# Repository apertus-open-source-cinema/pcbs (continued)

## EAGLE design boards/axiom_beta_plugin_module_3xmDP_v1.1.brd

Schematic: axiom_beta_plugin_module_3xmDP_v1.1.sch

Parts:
C1: C0402-B; 0402-B
C2, C3, C4, C5, C6, C7: C0603-B; 0603-B
LED1, LED2, LED3, LED4, LED5, LED6: LEDCHIPLED_0603; CHIPLED_0603
PCIE-NORTH: PCIE-36-AXIOM
PCIE-SOUTH: PCIE-36-AXIOM
R1: 10k; 0402-B
R2: 1k; 0402-B
R3, R4, R5, R6, R7, R8: R0402-B; 0402-B
U1: BR24G04NUX; DFN200X300X100-9N
U2, U3, U4: MIC209X; SOT95P280X145-5N
X1, X2, X3: MINI-DP-ADIS0013; ADIS0013

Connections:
C_!FAULT: LED4.C, U3.4 (!FAULT)
C_AUX_N: PCIE-NORTH.B9 (IO5), X2.17
C_AUX_P: PCIE-NORTH.B8 (IO4), X2.15
C_EN: PCIE-SOUTH.B11 (IO7), R5.1, U3.3 (EN)
C_HPD: PCIE-SOUTH.B10 (IO6), X2.18
C_ML0_N: PCIE-SOUTH.A17 (LVDS_4B), X2.3
C_ML0_P: PCIE-SOUTH.A16 (LVDS_4A), X2.1
C_ML1_N: PCIE-NORTH.A3 (LVDS_0B), X2.6
C_ML1_P: PCIE-NORTH.A2 (LVDS_0A), X2.4
C_ML2_N: PCIE-SOUTH.B17 (LVDS_5B), X2.9
C_ML2_P: PCIE-SOUTH.B16 (LVDS_5A), X2.7
C_ML3_N: PCIE-NORTH.A6 (LVDS_1B), X2.12
C_ML3_P: PCIE-NORTH.A5 (LVDS_1A), X2.10
C_PWR: C5.1, U3.5 (VOUT), X2.20
GND: C1.2, C2.2, C3.2, C4.2, C5.2, C6.2, C7.2, LED1.C, LED3.C, LED5.C, PCIE-NORTH.A1 (GND), PCIE-NORTH.A4 (GND), PCIE-NORTH.A7 (GND), PCIE-NORTH.A10 (GND), PCIE-NORTH.A12 (GND), PCIE-NORTH.A15 (GND), PCIE-NORTH.A18 (GND), PCIE-NORTH.B15 (GND), PCIE-NORTH.B18 (GND), PCIE-SOUTH.A1 (GND), PCIE-SOUTH.A4 (GND), PCIE-SOUTH.A7 (GND), PCIE-SOUTH.A10 (GND), PCIE-SOUTH.A12 (GND), PCIE-SOUTH.A15 (GND), PCIE-SOUTH.A18 (GND), PCIE-SOUTH.B15 (GND), PCIE-SOUTH.B18 (GND), R2.2, U1.1 (A0), U1.2 (A1), U1.3 (A2), U1.4 (GND), U1.EP, U2.2 (GND), U3.2 (GND), U4.2 (GND), X1.2, X1.5, X1.8, X1.11, X1.13, X1.14, X1.16, X1.19, X1.H1 (M), X1.H2 (M), X1.H3 (M), X1.H4 (M), X2.2, X2.5, X2.8, X2.11, X2.13, X2.14, X2.16, X2.19, X2.H1 (M), X2.H2 (M), X2.H3 (M), X2.H4 (M), X3.2, X3.5, X3.8, X3.11, X3.13, X3.14, X3.16, X3.19, X3.H1 (M), X3.H2 (M), X3.H3 (M), X3.H4 (M)
I2C_V: C1.1, PCIE-NORTH.B3 (V_I2C), R1.1, U1.8 (VCC)
unnamed: LED3.A, R5.2
unnamed: LED4.A, R6.2
unnamed: LED1.A, R3.2
unnamed: LED2.A, R4.2
unnamed: R1.2, R2.1, U1.7 (WP)
unnamed: LED5.A, R7.2
unnamed: LED6.A, R8.2
N_5V: PCIE-NORTH.B12 (5V)
N_!FAULT: LED2.C, U2.4 (!FAULT)
N_AUX_N: PCIE-NORTH.B11 (IO7), X1.17
N_AUX_P: PCIE-NORTH.B10 (IO6), X1.15
N_EN: PCIE-NORTH.B5 (IO1), R3.1, U2.3 (EN)
N_HPD: PCIE-NORTH.B4 (IO0), X1.18
N_ML0_N: PCIE-NORTH.A9 (LVDS_2B), X1.3
N_ML0_P: PCIE-NORTH.A8 (LVDS_2A), X1.1
N_ML1_N: PCIE-NORTH.A14 (LVDS_3B), X1.6
N_ML1_P: PCIE-NORTH.A13 (LVDS_3A), X1.4
N_ML2_N: PCIE-NORTH.B17 (LVDS_5B), X1.9
N_ML2_P: PCIE-NORTH.B16 (LVDS_5A), X1.7
N_ML3_N: PCIE-NORTH.A17 (LVDS_4B), X1.12
N_ML3_P: PCIE-NORTH.A16 (LVDS_4A), X1.10
N_PCIE_V: C2.1, C4.1, PCIE-NORTH.B13 (VCC), R4.1, R6.1, U2.1 (VIN), U3.1 (VIN)
N_PWR: C3.1, U2.5 (VOUT), X1.20
N_VCCIO: PCIE-NORTH.B14 (VCCIO)
SCL: PCIE-NORTH.B2 (SCL), U1.6 (SCL)
SDA: PCIE-NORTH.B1 (SDA), U1.5 (SDA)
S_5V: PCIE-SOUTH.B12 (5V)
S_!FAULT: LED6.C, U4.4 (!FAULT)
S_AUX_N: PCIE-NORTH.B7 (IO3), X3.17
S_AUX_P: PCIE-NORTH.B6 (IO2), X3.15
S_EN: PCIE-SOUTH.B5 (IO1), R7.1, U4.3 (EN)
S_HPD: PCIE-SOUTH.B4 (IO0), X3.18
S_IO2: PCIE-SOUTH.B6 (IO2)
S_IO3: PCIE-SOUTH.B7 (IO3)
S_IO4: PCIE-SOUTH.B8 (IO4)
S_IO5: PCIE-SOUTH.B9 (IO5)
S_ML0_N: PCIE-SOUTH.A3 (LVDS_0B), X3.3
S_ML0_P: PCIE-SOUTH.A2 (LVDS_0A), X3.1
S_ML1_N: PCIE-SOUTH.A6 (LVDS_1B), X3.6
S_ML1_P: PCIE-SOUTH.A5 (LVDS_1A), X3.4
S_ML2_N: PCIE-SOUTH.A14 (LVDS_3B), X3.9
S_ML2_P: PCIE-SOUTH.A13 (LVDS_3A), X3.7
S_ML3_N: PCIE-SOUTH.A9 (LVDS_2B), X3.12
S_ML3_P: PCIE-SOUTH.A8 (LVDS_2A), X3.10
S_PCIE_V: C6.1, PCIE-SOUTH.B13 (VCC), R8.1, U4.1 (VIN)
S_PWR: C7.1, U4.5 (VOUT), X3.20
S_VCCIO: PCIE-SOUTH.B14 (VCCIO)

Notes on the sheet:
AXIOM Beta Module
Copyright (C) 2015 H.Poetzl Licensed under CERN OHL v.1.2
Tripe PMOD Plugin Module
Info EEPROM
North DisplayPort
Center DisplayPort
South DisplayPort

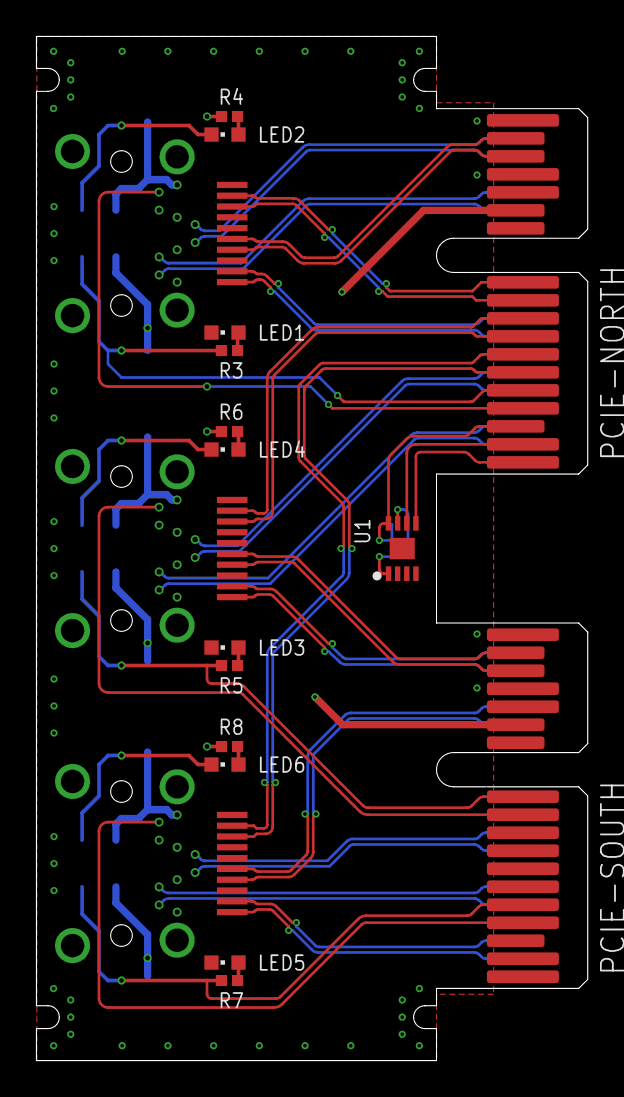
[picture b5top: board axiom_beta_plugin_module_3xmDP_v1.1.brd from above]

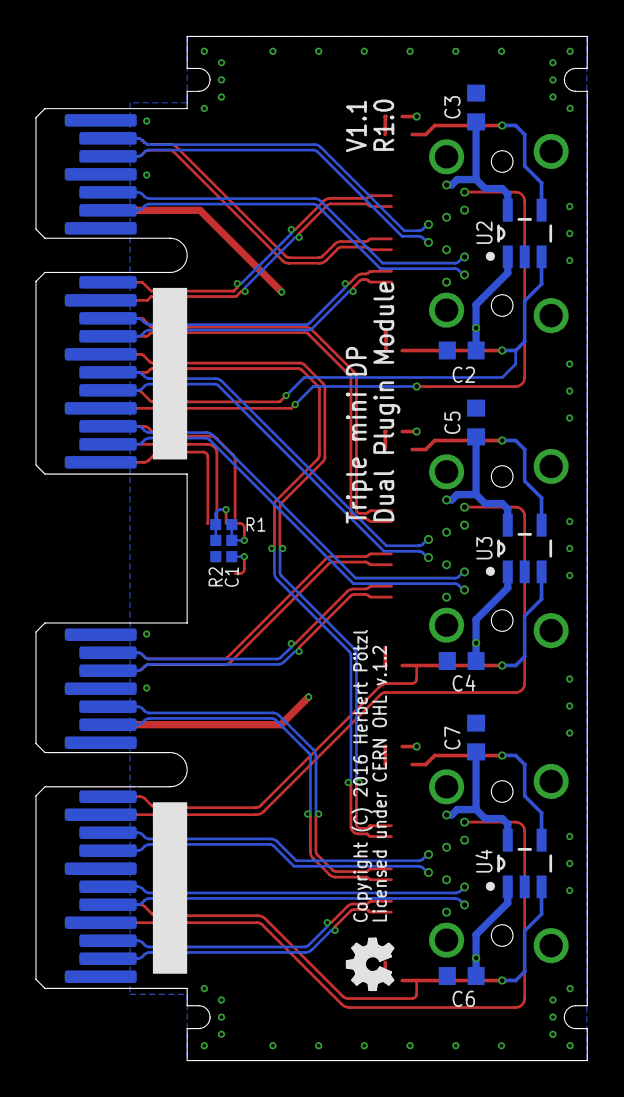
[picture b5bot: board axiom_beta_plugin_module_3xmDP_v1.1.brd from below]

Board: 4 copper layers, 30.6 x 56.9 mm, 31 parts (13 on the bottom side), 55 nets.

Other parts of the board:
LOGO1: OSHW_LOGO_FILLX0100-NT; OSHW_FILLX100_NOTEXT

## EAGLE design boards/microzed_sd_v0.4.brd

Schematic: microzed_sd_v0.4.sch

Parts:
C1, C2, C3, C4, C6: 1µ; C0402K
C5: 2n2; C0402K
D1: DIODE-MICROMELF-W; MICROMELF-W
DN: TPTP20R; TP20R
DP: TPTP20R; TP20R
GND: TPTP20R; TP20R
GP6, GP7: TPTP20R; TP20R
LOGO1: OSHW_LOGO_FILLX0100-NT; OSHW_FILLX100_NOTEXT
PWM: WIREPAD2,15/1,0; 2,15/1,0
Q1: NPN-TRANSISTOR_SOT23; SOT23
R1, R2: R-EU_R0603; R0603
R3: 10k; R0603
R4: 100R; R0402
R5: 2k2; R0402
R6, R7: 10k; R0402
T1, T2: PMR670UPE; SOT416
T3: PMR290UNE; SOT416
TACH: WIREPAD2,15/1,0; 2,15/1,0
U0: µZ-PMOD-NOHOLES; µZ-TOP-NOHOLES
U1: TXS02612; S-PWQFN-N24
U2: MCP23009-E/MG; QFN50P300X300X80-17N
U3: 74LVC1G98DW-7; SOT65P210X110-6N
U4, U5: LD6836TD/30P; SOT95P275X110-5N
U6: EMC2101-ACZL; SOP65P490X110-8N
U$1: APERTUS_LOGO334X100; APERTUS_LOGO_334X100
U$13: AXIOM_LOGO525X80; AXIOM_LOGO_525X80
VDD: WIREPAD2,15/1,0; 2,15/1,0
µSD0, µSD1: MICRO-SD3; TF-MICRO-SD_PP3

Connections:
A_CLK: U0.J5-4 (PMOD_D3), U1.9 (A_CLK)
A_CMD: U0.J5-3 (PMOD_D2), U1.4 (A_CMD)
A_DAT0: U0.J5-2 (PMOD_D1), U1.6 (A_DAT0)
A_DAT1: U0.J5-1 (PMOD_D0), U1.7 (A_DAT1)
A_DAT2: U0.J5-9 (PMOD_D6), U1.1 (A_DAT2)
A_DAT3: U0.J5-10 (PMOD_D7), U1.3 (A_DAT3)
B0_CLK: U1.19 (B0_CLK), µSD0.5
B0_CMD: U1.20 (B0_CMD), µSD0.3
B0_DAT0: U1.18 (B0_DAT0), µSD0.7
B0_DAT1: U1.16 (B0_DAT1), µSD0.8
B0_DAT2: U1.23 (B0_DAT2), µSD0.1
B0_DAT3: U1.22 (B0_DAT3), µSD0.2
B1_CLK: U1.13 (B1_CLK), µSD1.5
B1_CMD: U1.12 (B1_CMD), µSD1.3
B1_DAT0: U1.14 (B1_DAT0), µSD1.7
B1_DAT1: U1.15 (B1_DAT1), µSD1.8
B1_DAT2: U1.8 (B1_DAT2), µSD1.1
B1_DAT3: U1.10 (B1_DAT3), µSD1.2
CD0: U2.11 (GP2), µSD0.CD
CD1: U2.12 (GP3), µSD1.CD
DN: DN.TP, Q1.2 (E), R4.2
DP: C5.2, DP.TP, Q1.1 (B), Q1.3 (C), U6.2 (DP)
FAN: C6.2, PWM.1, T3.3 (D)
GND: C1.2, C2.2, C3.2, C4.2, GND.TP, R2.1, T3.2 (S), U0.J5-5 (GND), U0.J5-11 (GND), U0.JP4-1 (GND), U0.JP4-3 (GND), U1.2 (GND), U1.11 (GND), U1.EPAD (ECPAD), U2.1 (GND), U2.17 (GND), U3.2 (GND), U4.2 (GND), U5.2 (GND), U6.5 (GND), µSD0.6, µSD0.MT1 (MT), µSD0.MT2 (MT), µSD0.MT3 (MT), µSD0.MT4 (MT), µSD1.6, µSD1.MT1 (MT), µSD1.MT2 (MT), µSD1.MT3 (MT), µSD1.MT4 (MT)
GP6: GP6.TP, U2.15 (GP6)
GP7: GP7.TP, U2.16 (GP7)
unnamed: U2.13 (GP4), U3.1 (IN1)
unnamed: U2.14 (GP5), U3.6 (IN2)
unnamed: R1.1, R2.2, U2.6 (ADDR)
unnamed: R3.1, U2.7 (!RESET)
unnamed: C5.1, R4.1, U6.3 (DN)
unnamed: R5.2, T3.1 (G), U6.4 (FAN)
unnamed: D1.A, R7.2, U6.6 (!ALERT!/TACH)
PWR0: T1.1 (G), U2.9 (GP0), U4.3 (EN)
PWR1: T2.1 (G), U2.10 (GP1), U5.3 (EN)
SCL: U0.J5-7 (PMOD_D4), U2.4 (SCL), U6.8 (SMCLK)
SDA: U0.J5-8 (PMOD_D5), U2.5 (SDA), U3.3 (IN0), U6.7 (SMDATA)
SEL: U1.24 (SEL), U3.4 (Y)
TACH: D1.C, R6.2, TACH.1
VCC: R1.2, R3.2, R7.1, T1.2 (S), T2.2 (S), U0.J5-6 (VCC), U0.J5-12 (VCC), U1.5 (A_VCC), U2.3 (VDD), U3.5 (VCC), U6.1 (VDD)
VCC0: C2.1, T1.3 (D), U1.21 (B0_VCC), U4.5 (OUT), µSD0.4
VCC1: C4.1, T2.3 (D), U1.17 (B1_VCC), U5.5 (OUT), µSD1.4
VDD: C1.1, C3.1, C6.1, R5.1, R6.1, U0.JP4-2 (VDD), U4.1 (IN), U5.1 (IN), VDD.1

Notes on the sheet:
PMOD Dual SD/FAN Module
Copyright (C) 2014 H.Poetzl Licensed under CERN OHL v.1.1

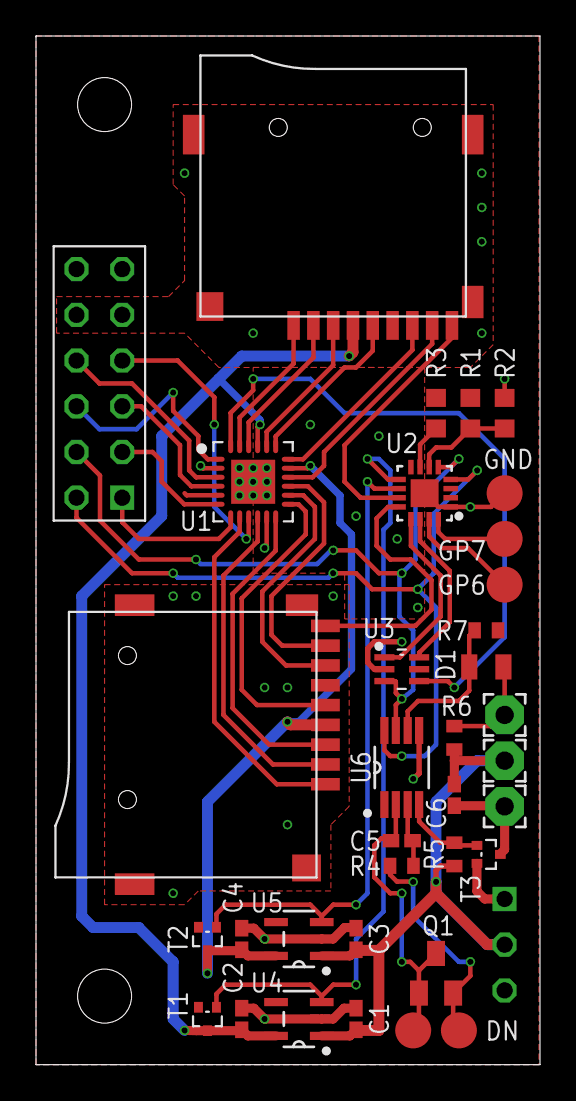
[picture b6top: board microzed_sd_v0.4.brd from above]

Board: 4 copper layers, 28.0 x 57.1 mm, 38 parts (3 on the bottom side), 43 nets.

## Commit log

2021-12-14 increase CI timeout
2021-12-14 fix some more problems
2021-12-15 use webp and add single board links / routes
2021-12-17 try ci sharding
2021-12-17 test
2021-12-17 test3
2021-12-17 test4
2021-12-17 test5
2021-12-17 fixup
2021-12-17 copy info.json to artifacts
2021-12-17 fix mv
2021-12-17 deploy: 92cfe49900b556528325c137cf39063338544431
2021-12-17 full
2021-12-17 deploy: bc60a2cc87d1ffd9ad937289c0f848cdc5142e1b
2021-12-21 add a simple readme
